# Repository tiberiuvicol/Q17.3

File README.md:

# Q17.3 - more than an audiophile approach to perfect sound

Q17.3 is a continuation of the <a href="https://github.com/tiberiuvicol/Q17-audiophile-amplifier">Q17 class B amplifier</a> based on current dumping principle.<br>
Use KiCad 7, or later, to open and edit source files.  KiCad 7 can be downloaded from CERN, https://www.kicad.org<br>
<b>LTSpice</b> - contain simulation asc file<br>

<br>
Click & Order your Q17.3 parts @ digikey https://www.digikey.co.uk/en/mylists/list/O9YXGXU6LF <br>
For STEREO or MULTICHANNEL multiply the order with the same parts. <br>
You may order your PCB at 

<br>
What is new ? <br>
Operational was changed to OPA828. This is one of the few SiGe devices on the market, with terrific performance and most important, sound quality is exceptional.
Current mirror was replaced with NDC7003P (PJS6839 is an alternative). This have 2 matched p-mos transistors on same substrate with same thermal Vgs deviation.<br>
Furthermore, by adding Q7, current mirror was upgraded to a Wilson one. This improve mirror stability and class A stage operation at high frequency.
In an atempt to make the amplifier more "popular", I have adopted jellybean parts as IRFP240/IRFP9240, 2N4401/2N4403 and 2N5551/2N5401. These are widely available from various manufacturers.
First stage after OPA828 is now a modified "a la" Borbely cascode, made with a well known jfet LSK170B/2SK170B and a depletion mosfet DN2535/DN2540. 
In addition, R10 and R13 have been reduced to 9R1. In case IRFP's get too hot (over 60Celsius), you may increase R10 and R13 to 10ohm.<br>
With this modifications, Q17 performance was considerably improved, both in measurement and listening.
<br>
If you have built this amplifier I would love to see your Q17 implementation. :-) <br>
<br>
Enjoy and thank you for reading !

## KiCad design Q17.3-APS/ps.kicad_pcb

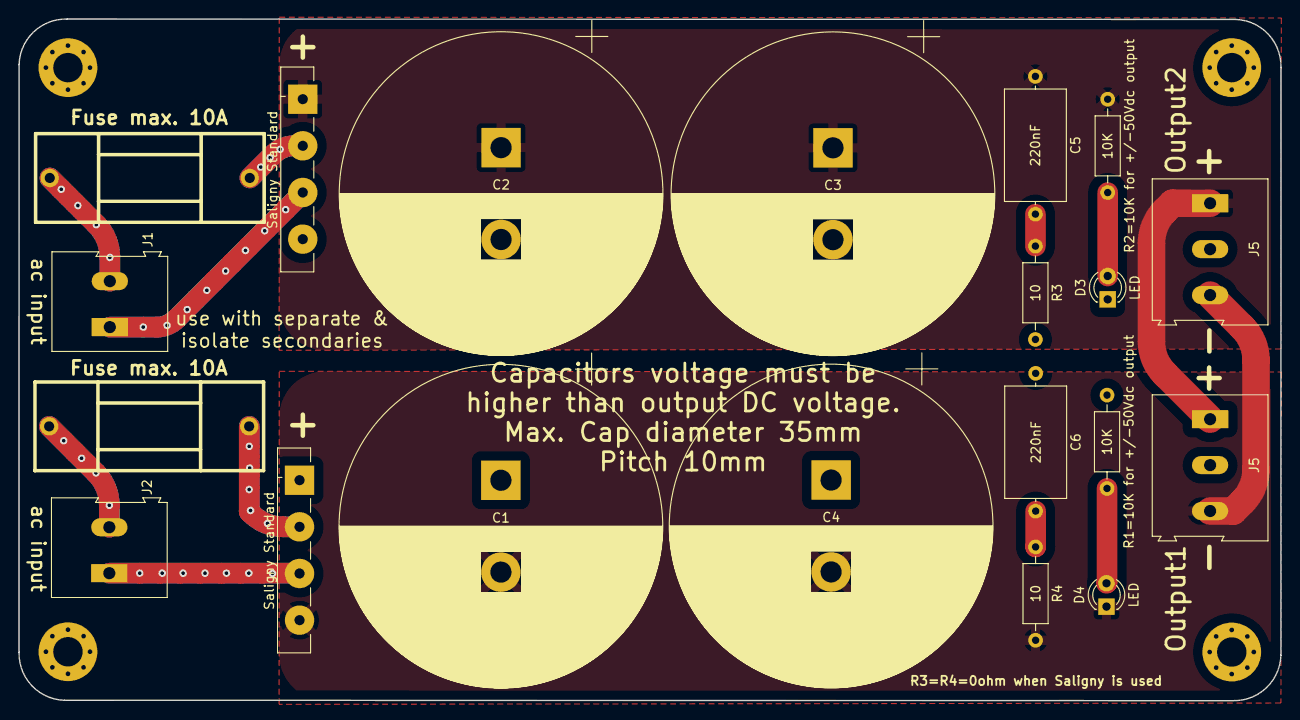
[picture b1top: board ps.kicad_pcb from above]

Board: 2 copper layers, 137.4 x 74.2 mm, 20 parts (0 on the bottom side), 11 nets.

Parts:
C1, C2, C3, C4: C_Polarized; CP_Radial_D35.0mm_P10.00mm_SnapIn
C5, C6: 220nF; C_Axial_L12.0mm_D6.5mm_P15.00mm_Horizontal
D3, D4: LED; LED_D3.0mm
F1, F2: Fuse max. 10A; fuse_holder_CQ-2
J1, J2: Conn_01x02_Female; TerminalBlock_Altech_AK300-2_P5.00mm
J5, J5#2: Conn_01x03_Female; TerminalBlock_Altech_AK300-3_P5.00mm
R1=10K for +/-50Vdc output, R2=10K for +/-50Vdc output: 10K; R_Axial_DIN0207_L6.3mm_D2.5mm_P10.16mm_Horizontal
R3, R4: 10; R_Axial_DIN0207_L6.3mm_D2.5mm_P10.16mm_Horizontal
Saligny Standard: Active_Bridge_+AA-; Diode_Bridge_Vishay_GBU
Saligny Standard#2: Active_Bridge_+AA-; Diode_Bridge_Vishay_GBU

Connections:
GNDPWR: C1.1, C2.2, C3.2, C4.1, C6.1, D3.1 (K), J5.2, J5#2.2, R1=10K for +/-50Vdc output.1, R3.2, Saligny Standard.4 (-), Saligny Standard#2.1 (+)
unnamed: C5.2, R3.1
unnamed: C6.2, R4.1
unnamed: F1.2, Saligny Standard.2 (~~)
unnamed: J1.1, Saligny Standard.3 (~~)
unnamed: F2.2, Saligny Standard#2.2 (~~)
unnamed: J2.1, Saligny Standard#2.3 (~~)
unnamed: C1.2, C4.2, D4.1 (K), J5.3, J5#2.3, R4.2, Saligny Standard#2.4 (-)
unnamed: D3.2 (A), R2=10K for +/-50Vdc output.2
unnamed: D4.2 (A), R1=10K for +/-50Vdc output.2
unnamed: C2.1, C3.1, C5.1, J5.1, J5#2.1, R2=10K for +/-50Vdc output.1, Saligny Standard.1 (+)

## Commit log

2023-07-30 Q17.3 ltspice arc file
    Q17.3 ltspice arc file
2023-07-30 Create KiCad source
2023-07-30 KiCad source files
    PCB KiCad source files
2023-07-30 KiCAD source files
    PCB KiCad source files. Open with version 7.
2023-08-06 Dimensions file
    Dimensions file
2023-08-06 STEP file
